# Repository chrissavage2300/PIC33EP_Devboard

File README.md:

# dsPIC33EP Devboard
This is a little dev board I created to use the PIC33EP series. It may or may not work with other PICs from that series. I made two versions, one for the 28 DIP package and the other is for the SSOP package. Made to fit on a breadboard.

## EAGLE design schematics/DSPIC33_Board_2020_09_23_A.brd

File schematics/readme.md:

9/23/2020-Boards Designed and Ordered. Total cost $8.00 for 3 at OSH park

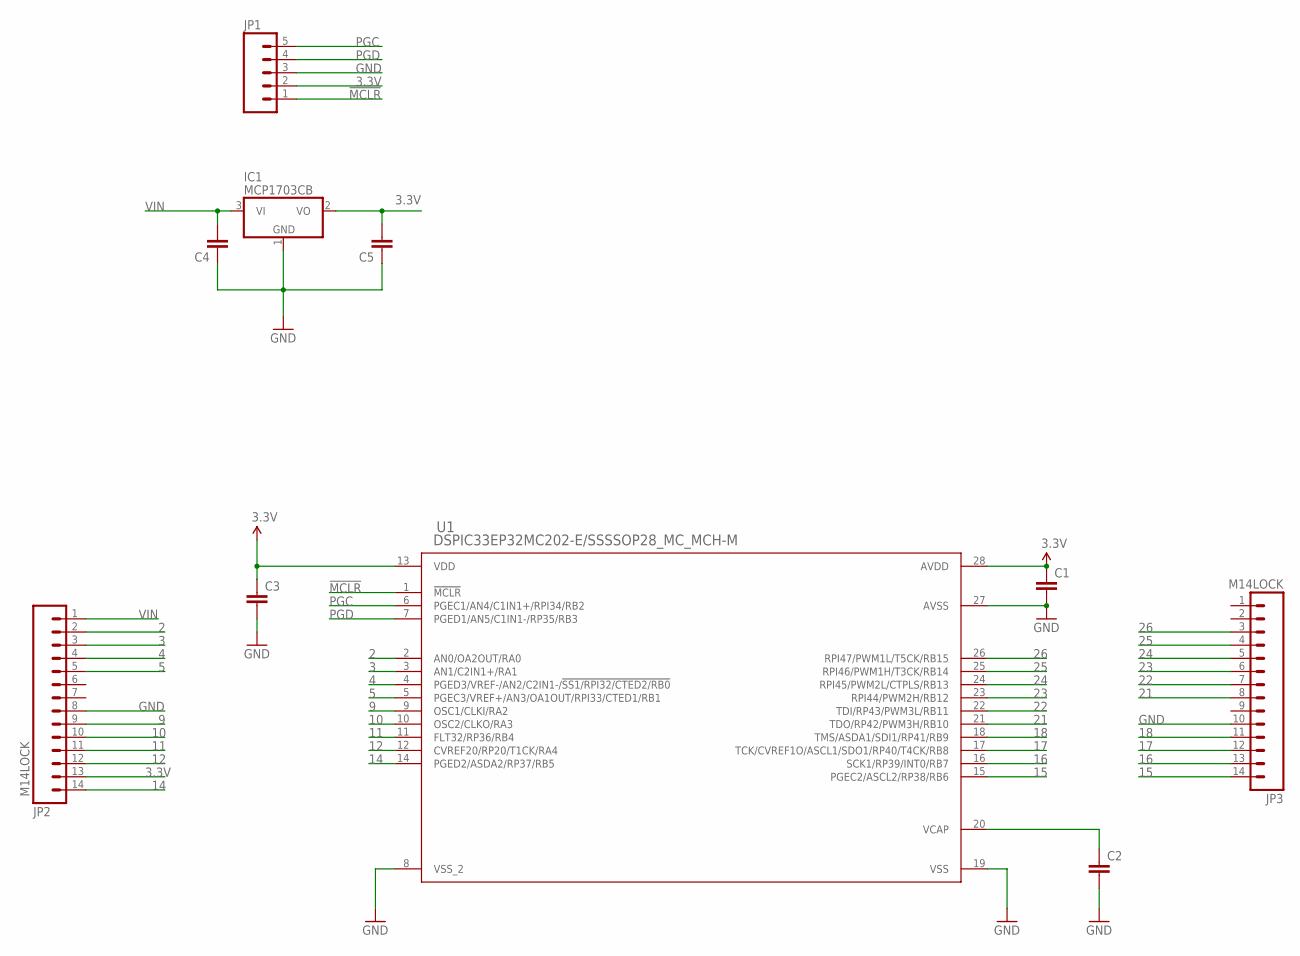
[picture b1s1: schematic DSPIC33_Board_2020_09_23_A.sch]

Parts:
C1, C2, C3, C4, C5: CAP1206; 1206
IC1: MCP1703CB; SOT23
JP1: M05LOCK; 1X05_LOCK
JP2, JP3: M14LOCK; 1X14_LOCK
U1: DSPIC33EP32MC202-E/SSSSOP28_MC_MCH-M; SSOP28_MC_MCH-M

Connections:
2: JP2.2, U1.2 (AN0/OA2OUT/RA0)
3: JP2.3, U1.3 (AN1/C2IN1+/RA1)
3.3V: C1.1, C3.1, C5.2, IC1.2 (VO), JP1.2, JP2.13, U1.13 (VDD), U1.28 (AVDD)
4: JP2.4, U1.4 (PGED3/VREF-/AN2/C2IN1-/!SS1/RPI32/CTED2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)
5: JP2.5, U1.5 (PGEC3/VREF+/AN3/OA1OUT/RPI33/CTED1/RB1)
9: JP2.9, U1.9 (OSC1/CLKI/RA2)
10: JP2.10, U1.10 (OSC2/CLKO/RA3)
11: JP2.11, U1.11 (FLT32/RP36/RB4)
12: JP2.12, U1.12 (CVREF20/RP20/T1CK/RA4)
14: JP2.14, U1.14 (PGED2/ASDA2/RP37/RB5)
15: JP3.14, U1.15 (PGEC2/ASCL2/RP38/RB6)
16: JP3.13, U1.16 (SCK1/RP39/INT0/RB7)
17: JP3.12, U1.17 (TCK/CVREF1O/ASCL1/SDO1/RP40/T4CK/RB8)
18: JP3.11, U1.18 (TMS/ASDA1/SDI1/RP41/RB9)
21: JP3.8, U1.21 (TDO/RP42/PWM3H/RB10)
22: JP3.7, U1.22 (TDI/RP43/PWM3L/RB11)
23: JP3.6, U1.23 (RPI44/PWM2H/RB12)
24: JP3.5, U1.24 (RPI45/PWM2L/CTPLS/RB13)
25: JP3.4, U1.25 (RPI46/PWM1H/T3CK/RB14)
26: JP3.3, U1.26 (RPI47/PWM1L/T5CK/RB15)
!MCLR: JP1.1, U1.1 (!MCLR)
GND: C1.2, C2.1, C3.2, C4.1, C5.1, IC1.1 (GND), JP1.3, JP2.8, JP3.10, U1.8 (VSS_2), U1.19 (VSS), U1.27 (AVSS)
unnamed: C2.2, U1.20 (VCAP)
PGC: JP1.5, U1.6 (PGEC1/AN4/C1IN1+/RPI34/RB2)
PGD: JP1.4, U1.7 (PGED1/AN5/C1IN1-/RP35/RB3)
VIN: C4.2, IC1.3 (VI), JP2.1

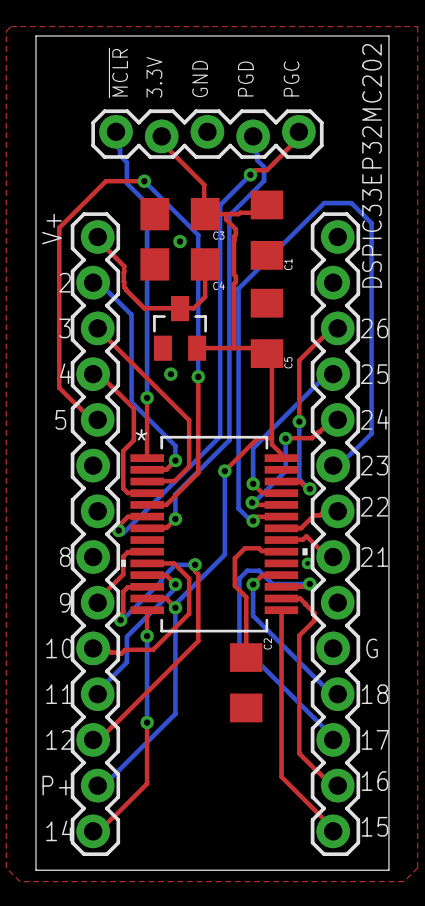
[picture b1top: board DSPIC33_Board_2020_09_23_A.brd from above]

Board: 2 copper layers, 19.6 x 46.3 mm, 10 parts (0 on the bottom side), 26 nets.

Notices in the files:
parts and their libraries:
SparkFun-Passives: Licensing: Creative Commons ShareAlike 4.0 International - https://creativecommons.org/licenses/by-sa/4.0
COPYRIGHT: Copyright (C) 2018 Accelerated Designs. All rights reserved
